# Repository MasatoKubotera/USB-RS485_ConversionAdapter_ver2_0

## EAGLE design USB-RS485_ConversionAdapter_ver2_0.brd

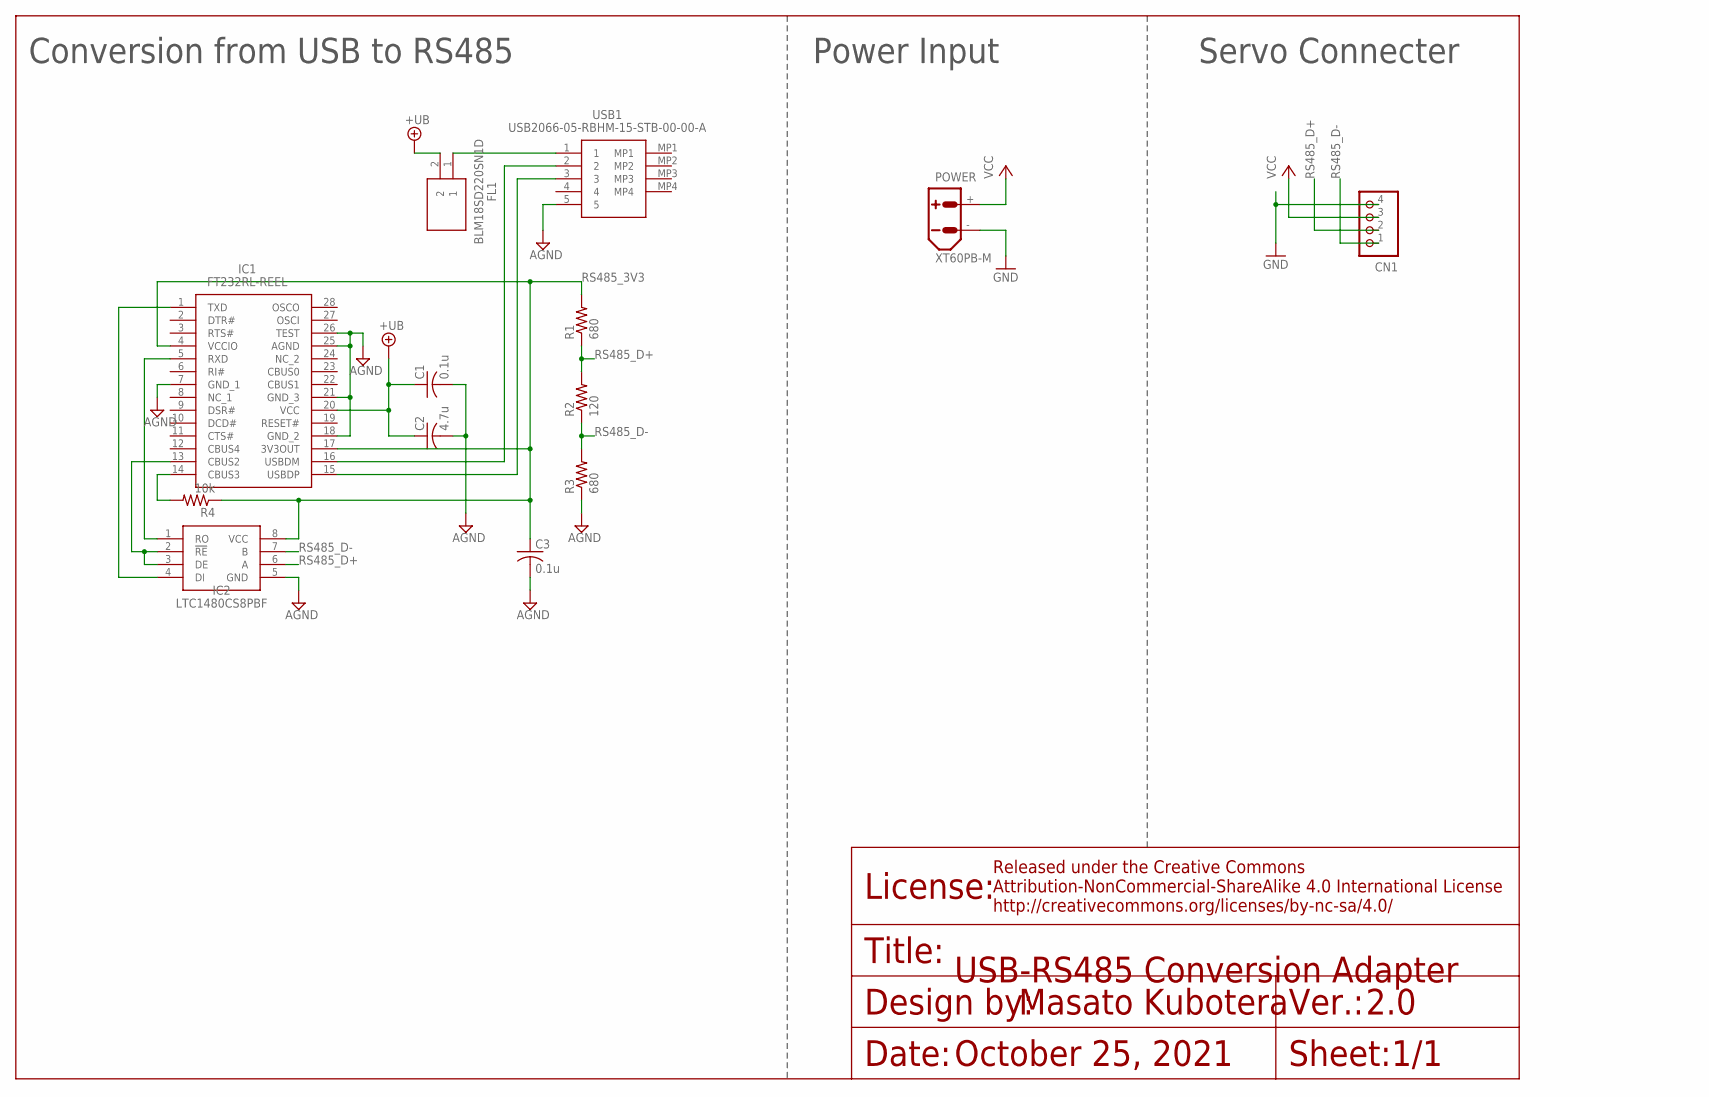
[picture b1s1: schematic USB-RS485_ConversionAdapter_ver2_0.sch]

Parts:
C1, C3: 0.1u; C1608
C2: 4.7u; C1608
CN1: B4B-XH-A
FL1: BLM18SD220SN1D; BLM18AG102BH1D
IC1: FT232RL-REEL; SOP65P778X200-28N
IC2: LTC1480CS8PBF; SOIC127P599X175-8N
POWER: XT60PB-M
R1, R3: 680; R0603
R2: 120; R0603
R4: 10k; R0603
USB1: USB2066-05-RBHM-15-STB-00-00-A; USB206605RBHM15STB0000A

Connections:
+UB: C1.1, C2.1, FL1.2, IC1.20 (VCC)
AGND: C1.2, C2.2, C3.2, IC1.7 (GND_1), IC1.18 (GND_2), IC1.21 (GND_3), IC1.25 (AGND), IC1.26 (TEST), IC2.5 (GND), R3.1, USB1.5
GND: CN1.4, POWER.-
RS485_1: IC1.14 (CBUS3), R4.2
RS485_2: IC1.13 (CBUS2), IC2.2 (!RE), IC2.3 (DE)
RS485_3V3: C3.1, IC1.4 (VCCIO), IC1.17 (3V3OUT), IC2.8 (VCC), R1.2, R4.1
RS485_D+: CN1.2, IC2.6 (A), R1.1, R2.2
RS485_D-: CN1.1, IC2.7 (B), R2.1, R3.2
RXD: IC1.5 (RXD), IC2.1 (RO)
TXD: IC1.1 (TXD), IC2.4 (DI)
USB_5V: FL1.1, USB1.1
USB_D+: IC1.15 (USBDP), USB1.3
USB_D-: IC1.16 (USBDM), USB1.2
VCC: CN1.3, POWER.+

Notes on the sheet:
Conversion from USB to RS485
Power Input
Servo Connecter
October 25, 2021
USB-RS485 Conversion Adapter
2.0
1/1

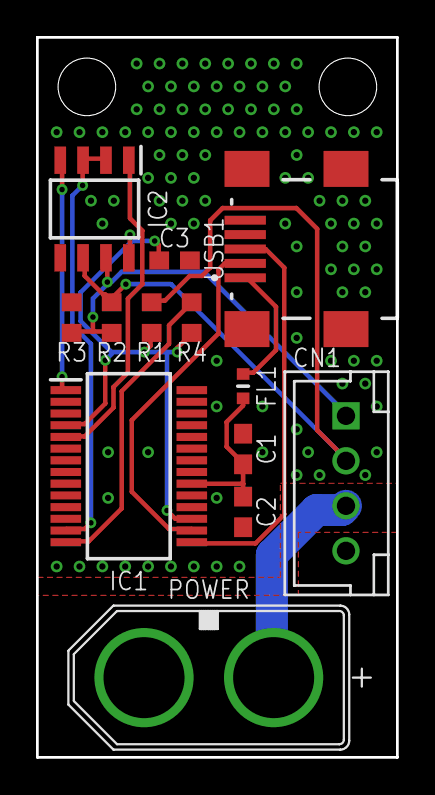
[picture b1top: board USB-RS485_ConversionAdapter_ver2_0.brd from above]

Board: 2 copper layers, 20.0 x 40.0 mm, 13 parts (0 on the bottom side), 14 nets.

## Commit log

2022-09-27 Initial upload of data

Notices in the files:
parts and their libraries:
Frame: Released under the Creative Commons
Attribution-NonCommercial-ShareAlike 4.0 International License
http://creativecommons.org/licenses/by-nc-sa/4.0
